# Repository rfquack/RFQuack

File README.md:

[![PlatformIO CI][ci-shield]][ci-url]
[![Contributors][contributors-shield]][contributors-url]
[![Forks][forks-shield]][forks-url]
[![Stargazers][stars-shield]][stars-url]
[![Issues][issues-shield]][issues-url]

<!-- PROJECT LOGO -->
<br />
<div align="center">

  <h3 align="center">RFQuack</h3>

  <p align="center">
    The only RF-analysis tool that quacks!
    <br />
    <br />
    <a href="https://rfquack.org"><strong>Documentation</strong></a>
    |
    <a href="https://arxiv.org/abs/2104.02551"><strong>Research Paper</strong></a>
    <br />
    <br />
    <a href="https://www.youtube.com/playlist?list=PL8hbvIylvVegA6ES-UUfd6sgK-MFNciz5">View Demo</a>
    ·
    <a href="https://github.com/rfquack/RFQuack/issues">Report Bug</a>
    ·
    <a href="https://github.com/rfquack/RFQuack/issues">Request Feature</a>
  </p>
</div>

<!-- ABOUT THE PROJECT -->

## About RFQuack

RFQuack is a versatile RF-analysis tool that allows you to sniff, analyze, and transmit data over the air.

Similarly to RFCat RFQuack has a Python-based scriptable shell that allows you to set parameters, receive, transmit, and so on.

<p align="right">(<a href="#readme-top">back to top</a>)</p>

## Supported Radios

We porting from (and contribute back to) [RadioLib](https://github.com/jgromes/RadioLib). So far, we support:

* __CC1101__ OOK, 2-FSK, 4-FSK, MSK radio module
* __nRF24L01__ 2.4 GHz module
* __RF69__ FSK, OOK radio module

## Supported Arduino Platforms

In principle, RFQuack can run on any board and platform supported by [PlatformIO](https://docs.platformio.org). So far, we tested the following boards:

* [**ESP32**](https://github.com/espressif/rduino-esp32) - ESP32-based boards
* [**Teensy**](https://github.com/PaulStoffregen/cores) - Teensy 2.x, 3.x and 4.x boards

<!-- GETTING STARTED -->
## Getting Started

This is an example of how you may give instructions on setting up RFQuack.

### Prerequisites

You'll need the Protbuf Compiler, a sane Python 3.10, and PlatformIO (which itself requires some dependencies):

- Protobuf Compiler
- Python 3.10.x
- PlatformIO

For more details, please refer to the [Documentation](https://rfquack.org).

<p align="right">(<a href="#readme-top">back to top</a>)</p>

<!-- INSTALLATION -->
## Installation

An easy way to quick start is to have an ESP32 board and a CC1101 and/or RF69 (easier to find) radio module.

```bash
git clone --recursive https://github.com/rfquack/RFQuack
cd RFQuack
pip install -r requirements.pip
vim build.env  # set your parameters and :wq
make clean build flash
```

For more details, please refer to the [Documentation](https://rfquack.org).

<p align="right">(<a href="#readme-top">back to top</a>)</p>

<!-- USAGE -->
## Usage

An easy way to quick start is to connect the dongle via USB and use the CLI.

```shell
$ rfq tty -P /dev/ttyUSB0
2019-04-10 18:04:31 local RFQuack[20877] INFO Transport initialized
2019-04-10 18:04:31 local RFQuack[20877] INFO Transport initialized (QoS = 2): mid = 2

...

RFQuack(/dev/ttyUSB0, 115200,8,N,1)> q.radioA.set_modem_config(modulation="OOK", carrierFreq=434.437)

result = 0
message = 2 changes applied and 0 failed.

RFQuack(/dev/ttyUSB0, 115200,8,N,1)> q.radioA.rx()

result = 0
message =
...
```

For more details, please refer to the [Documentation](https://rfquack.org).

<!-- ROADMAP -->
## Roadmap

- [ ] Add all relevant [RadioLib](https://github.com/jgromes/RadioLib) modules
- [ ] Test with more than 2 radio modules
- [ ] Revisit Python CLI source code and use typed Python 3
- [ ] Integrate with URH and GNU Radio
- [ ] Make a web UI

See the [open issues](https://github.com/rfquack/RFQuack/issues) for a full list of proposed features (and known issues).

<p align="right">(<a href="#readme-top">back to top</a>)</p>

<!-- CONTRIBUTING -->
## Contributing

Contributions are what make the open source community such an amazing place to learn, inspire, and create. Any contributions you make are **greatly appreciated**.

If you have a suggestion that would make this better, please fork the repo and create a pull request. You can also simply open an issue with the proper template.

Don't forget to give the project a star! Thanks again!

1. Fork the project
2. Create your feature branch (`git checkout -b feature/AmazingFeature`)
3. Commit your changes (`git commit -m 'Add some AmazingFeature'`)
4. Run simple integration tests (`make clean build`)
4. Push to the branch (`git push origin feature/AmazingFeature`)
5. Open a Pull Request

<p align="right">(<a href="#readme-top">back to top</a>)</p>

<!-- LICENSE -->
## License

Distributed under the GPL 2 License. See `LICENSE` for more information.

<p align="right">(<a href="#readme-top">back to top</a>)</p>

## Acknowledgments

RFQuack wouldn't exist without the inspiration, feedback, and help received from related tools and awesome humans:

* [RFCat](https://github.com/atlas0fd00m/rfcat)
* [RadioLib](https://github.com/jgromes/RadioLib)
* [RadioHead](https://www.airspayce.com/mikem/arduino/RadioHead/)
* [URH](https://github.com/jopohl/urh)

<p align="right">(<a href="#readme-top">back to top</a>)</p>

<!-- MARKDOWN LINKS & IMAGES -->
<!-- https://www.markdownguide.org/basic-syntax/#reference-style-links -->
[contributors-shield]: https://img.shields.io/github/contributors/rfquack/RFQuack.svg?style=for-the-badge
[contributors-url]: https://github.com/rfquack/RFQuack/graphs/contributors
[forks-shield]: https://img.shields.io/github/forks/rfquack/RFQuack.svg?style=for-the-badge
[forks-url]: https://github.com/rfquack/RFQuack/network/members
[stars-shield]: https://img.shields.io/github/stars/rfquack/RFQuack.svg?style=for-the-badge
[ci-url]: https://github.com/rfquack/RFQuack/actions/workflows/build.yml
[ci-shield]: https://img.shields.io/github/workflow/status/rfquack/RFQuack/PlatformIO%20CI?style=for-the-badge
[stars-url]: https://github.com/rfquack/RFQuack/stargazers
[issues-shield]: https://img.shields.io/github/issues/rfquack/RFQuack.svg?style=for-the-badge
[issues-url]: https://github.com/rfquack/RFQuack/issues
[license-shield]: https://img.shields.io/github/license/rfquack/RFQuack.svg?style=for-the-badge
[license-url]: https://github.com/rfquack/RFQuack/blob/master/LICENSE

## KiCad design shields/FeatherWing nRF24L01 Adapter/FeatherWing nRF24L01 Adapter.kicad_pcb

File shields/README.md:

# Feather Huzzah Shields

We provide two reference shields that work on Feather Huzzah (one for ESP8266 and the other for ESP32), V-Chip's VT-CC112x module and E01-ML01SP2 module (nRF24L01 + PA + PLNA).

## License

Our design is licensed as RFQuack main project, including the symbol and footprint for VT-CC112x.

Referred footprints and symbols, including but not limited to FeatherWing (DIM), are either MIT, Apache, or simply CC0.

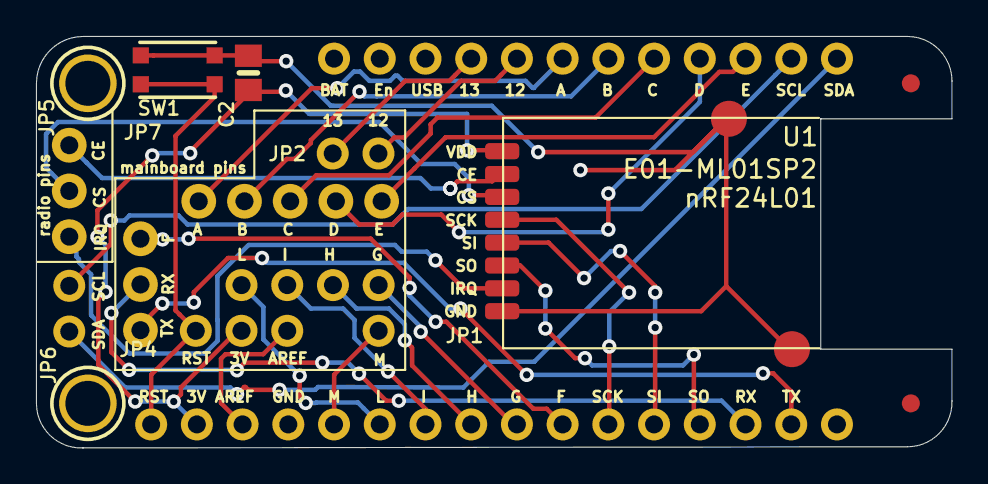
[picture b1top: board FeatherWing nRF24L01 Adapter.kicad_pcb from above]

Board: 2 copper layers, 50.9 x 22.9 mm, 14 parts (0 on the bottom side), 27 nets.

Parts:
C2: 47µF; 0805-NO
FID1, FID2: FIDUCIAL; FIDUCIAL_1MM
JP1: HEADER-1X970MIL; 1X09_ROUND_70
JP2: HEADER-1X570MIL; 1X02_ROUND
JP4, JP5: HEADER-1X376MIL; 1X03_ROUND_76
JP6: HEADER-1X2ROUND; 1X02_ROUND
JP7: HEADER-1X576MIL; 1X05_ROUND_76
MS1: FEATHERWING_NOHOLES
SW1: SWITCH_TACT_SMT4.6X2.8; BTN_KMR2_4.6X2.8
U1: nRF24L01_PA_LNA_E01_ML01SP2; E01-ML01SP2
U$7, U$8: MOUNTINGHOLE2.5; MOUNTINGHOLE_2.5_PLATED

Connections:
3.3V: C2.2, JP1.8, MS1.2, U1.1
/A: JP7.1, MS1.23
/AREF: JP1.7, MS1.3
/B: JP7.2, MS1.22
/C: JP7.3, MS1.21
/CE: JP5.3, U1.2
/CS: JP5.2, U1.3
/D: JP7.4, MS1.20
/E: JP7.5, MS1.19
/F: JP4.1, MS1.10
/G: JP1.1, MS1.9
/H: JP1.2, MS1.8
/I: JP1.3, MS1.7
/IRQ: JP5.1, U1.7
/L: JP1.4, MS1.6
/M: JP1.5, MS1.5
/MISO: MS1.13, U1.6
/MOSI: MS1.12, U1.5
/RST: JP1.9, MS1.1, SW1.B, SW1.B'
/RX: JP4.2, MS1.14
/SCK: MS1.11, U1.4
/TX: JP4.3, MS1.15
GND: C2.1, SW1.A, SW1.A', U1.8, U1.9, U1.10
unnamed: JP2.1, MS1.25
unnamed: JP2.2, MS1.24
unnamed: JP6.1, MS1.18
unnamed: JP6.2, MS1.17

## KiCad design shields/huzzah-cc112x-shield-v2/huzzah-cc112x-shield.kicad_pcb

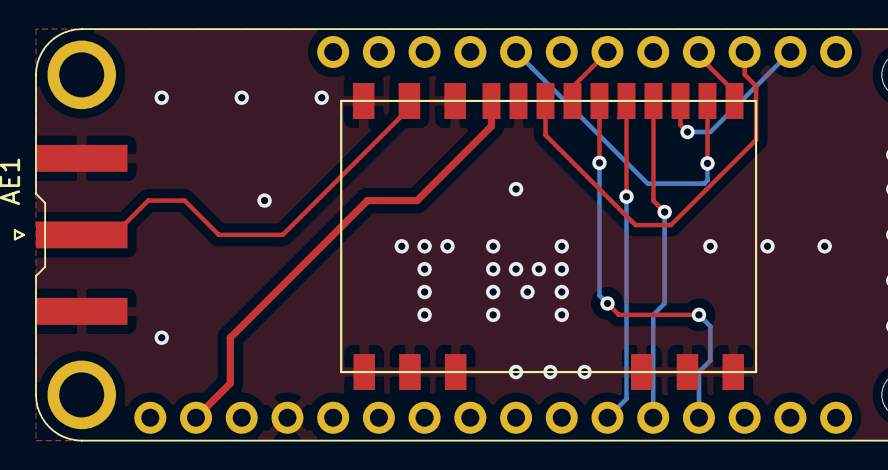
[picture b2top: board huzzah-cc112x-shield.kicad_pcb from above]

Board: 2 copper layers, 3 parts (0 on the bottom side), 11 nets.

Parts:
AE1: Antenna; SMA_Amphenol_132289_EdgeMount
MS1: FEATHERWING; FEATHERWING_DIM
U1: VT-CC112x-433M

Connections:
/3V3: MS1.2, U1.10
/CS: MS1.19, U1.8
/GND: AE1.2, MS1.4, U1.9, U1.11, U1.13, U1.14, U1.15, U1.16, U1.17, U1.18, U1.19
/GPIO3: MS1.24, U1.2
/ISR: MS1.18, U1.3
/ISR_PKT: MS1.22, U1.7
/RST: MS1.20, U1.1
/SCLK: MS1.11, U1.5
/SI: MS1.12, U1.4
/SO: MS1.13, U1.6
unnamed: AE1.1, U1.12

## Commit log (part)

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2019-05-07 Merge
2019-05-07 Fixing README
2019-05-07 Fixed Python syntax in the README.md
2019-10-26 Added missing configuration example for RFQuack-huzzah-rf69hw Added example credentials file Updated .gitignore to track example configuration for scret files (*credentials*.example)
2019-11-04 Added API support for fixed/variable packet format
2019-11-04 added example for RFQuack-huzzah32-rf69hw
2019-11-04 fixed examples to avoid conflicts with RadioHead
2019-11-04 fixed banner
2019-11-04 support for variable/fixed packet format
2019-11-04 regenerated protobuf python types
2019-11-04 default TX repeat value
2019-11-04 fixed buggy log printer
2019-11-04 macro comment for dev output
2019-11-05 CLI now lives in separate repo at rfquack/RFQuack-cli
2019-11-05 image align in README
2019-11-15 added FeatherWing nRF24L01 adapter
2019-11-15 changed nRF24 module to E01-ML01SP2
2019-12-08 Switch to RadioLib + Multiple Radio Support
2019-12-09 Removed references to RadioHAL
2019-12-10 Minor fixes.
2019-12-16 Added .pio* ignore pattern
2019-12-16 Removed old examples from RadioLib branch
2019-12-16 Snapshot
2019-12-17 [CC1101] Stop FIFO polling after 10mS
2019-12-17 User Serial1 for logging
2019-12-17 Added pio* ignore pattern
2019-12-17 Added makefile job to make examples
2020-01-22 [WIP] Modularization
2020-01-23 Modularization
2020-02-18 Fixed wrong return type
2020-02-19 [Modules] Better reply
2020-02-20 [Radio] Added setPromiscuousMode, getRSSI, isCarrierDetected
2020-02-20 Examples updated
2020-02-20 Examples setup updated
2020-02-20 Minor fixes + warnings fixes
2020-02-20 Moved module's hooks to a separated folder + documentation
2020-02-20 Yet another refactor to rfquack_radio.h
2020-02-25 Added mouse jack module.
2020-02-27 Fix rfquack_transport_setup()
2020-02-27 Removed useless loop
2020-02-28 Added parameter 'wait_time' in FrequencyScannerModule
2020-02-28 Small fixes
2020-03-02 [nRF24] Driver fix.
2020-03-03 Added HUZZAH32 as build target
2020-03-03 Typo
2020-03-04 Missing directory
2020-03-16 HelloWorldModule sample module
2020-04-09 Set a longer keep-alive value
2020-04-10 Added getChipName(), used for presets in FrequencyScannerModule
2020-04-10 [CC1101] Better gain settings + added method for manual calibration.
2020-04-10 Moved RadioLib dependency to https://github.com/rfquack/RadioLib
2020-04-10 [GuessingModule] Documentation and stop() method
2020-04-10 [nRF24] Missing writeRegister() implementation.
2020-04-10 Removed HelloWorldModule.h from pre-loaded modules
2020-04-11 [Docker] Automatically fill RFQUACK_TOPIC_PREFIX with an UUID
2020-04-11 [Examples] Stressing the fact that RFQUACK_TOPIC_PREFIX should be unique.
2020-04-11 [Keywords] Removed unsupported radios.
2020-04-11 [Transport] Added broadcast topic "any" to address any dongle: Example: any/in/get/...
2020-05-01 Small fixes + time statistics.
2020-05-13 Added supporto for MQTT over SSL
2020-05-14 Small fix
2020-05-15 Added .vscode/*
2020-05-15 Added lib/nanopb to ignore patterns
2020-05-15 Removed images + promoted section
2020-05-15 Nanopb latest version
2020-05-15 Pipfile to manage Python deps
2020-11-24 Client ID matches Unique ID
2020-11-27 Firmware compatible with NetQuack
2021-04-06 Adding RFM69
2021-04-06 Added projects section
2021-04-12 Added new shield
2021-04-12 Updated deps and EP
2021-04-12 Updated README.md with build-only example
2021-04-13 Smarter helper Makefile now supports flashing
2021-04-13 New repo URL in library.properties
2021-04-13 Fixed my-entrypoint.sh to build only or upload
2021-04-14 Using God mode
2021-04-16 Missing `_mod->`
2021-04-21 Removed truncated comment
2021-04-21 Added new modulation schemes
2021-04-24 Switched to submodule for RadioLib
2021-06-02 Bump urllib3 from 1.26.4 to 1.26.5
    Bumps [urllib3](https://github.com/urllib3/urllib3) from 1.26.4 to 1.26.5.
    - [Release notes](https://github.com/urllib3/urllib3/releases)
    - [Changelog](https://github.com/urllib3/urllib3/blob/main/CHANGES.rst)
    - [Commits](https://github.com/urllib3/urllib3/compare/1.26.4...1.26.5)
    ---
    updated-dependencies:
2021-09-16 Updated RadioLib to master HEAD
2021-09-16 Upgraded Python deps
2021-09-16 Removed Protobuf Python-compiled header
2021-09-19 Add default src/main.cpp to ignore patterns
2021-09-19 Cleaned white spaces and newlines
2021-09-19 Added mock platformio.ini file
2021-09-19 Added pre/post scripts
2021-09-19 Reformatted and updated library.json
2021-09-19 Added pio run
2021-09-19 Added s/pio/platformio/
2021-09-20 Added pipenv run
2021-09-20 Added pio lib install
2021-09-24 Workflow working on act
2021-09-27 Removed macos-latest and windows-latest
2022-01-26 Added proto target to Makefile
    Reinstated proto target in Makefile to resolve build issues.
2022-06-03 Bump bottle from 0.12.19 to 0.12.20
    Bumps [bottle](https://github.com/bottlepy/bottle) from 0.12.19 to 0.12.20.
    - [Release notes](https://github.com/bottlepy/bottle/releases)
    - [Changelog](https://github.com/bottlepy/bottle/blob/master/docs/changelog.rst)
    - [Commits](https://github.com/bottlepy/bottle/compare/0.12.19...0.12.20)
    ---
    updated-dependencies:
2022-08-24 updated outdated packages
2022-08-24 added new exmaple
2022-08-30 clean up
2022-08-30 rollback board
2022-08-30 README linting
2022-08-30 Added favicon square format
2022-09-02 - Code of conduct - Contributing guidelines - Security policy - Issue templates
2022-09-02 Update contribution guidelines
2022-09-03 radiolib 5.3.0 changes (#23)
2022-09-03 Updated RadioLib
2022-09-23 Bump protobuf from 3.18.0 to 3.18.3
    Bumps [protobuf](https://github.com/protocolbuffers/protobuf) from 3.18.0 to 3.18.3.
    - [Release notes](https://github.com/protocolbuffers/protobuf/releases)
    - [Changelog](https://github.com/protocolbuffers/protobuf/blob/main/generate_changelog.py)
    - [Commits](https://github.com/protocolbuffers/protobuf/compare/v3.18.0...v3.18.3)
    ---
    updated-dependencies:
2022-11-07 adding missing code to CC1101 and implementing full promiscious mode with custom or missing syncwords (needs GPIO02 connection to work)
2022-11-15 Moved getters/setters into RadioLib
2022-11-15 Better code documentation
2022-11-15 Ignoring docs/reference
2022-11-15 Compact Dockerfile
2022-11-15 Compact library.json
2022-11-15 The Makefile is the new entry point
2022-11-15 No entry point for docker
2022-11-15 Removing pre/post PlatformIO build scripts
2022-11-15 Simpler examples
2022-11-15 Removed client/
2022-11-15 build.env with 3 RFs
2022-11-16 make clean now removes Protobuf-generated code
2022-11-16 mypy protobuf-types
2022-11-16 Build system advancements
2022-11-16 GA: removed apt deps
2022-11-16 GA: bump python version
2022-11-16 GA: RadioLib is now a dep
2022-11-16 GA: checkout submodules
2022-11-16 First proper release of the docs
2022-11-16 GA: MkDocs + py310
2022-11-16 Improving README
2022-11-18 Fixes minor typo on support faq page
2022-11-18 Fixes minor typo on support faq page (#29)
2022-11-20 New rfquack/RadioLib version
2022-11-21 _syncWordLength is now in RFQCC1101 wrapper
2022-11-21 [RadioLib] PR#613 reviews
2022-11-26 Adding RadioLib as a dependency
2022-11-26 New requirements.pip
2022-11-26 Docs update
2022-11-26 Updated lib/RadioLib
2022-11-26 - No more SoftwareSerial logging - logging goes all to `Serial` if enabled
2022-11-26 Using logging macros
2022-11-27 Update RadioLib
2022-11-27 Send message at boot to help CLI find the dongle
2022-11-27 Cherry picked some changes from @akito45's fork
2022-11-28 Update Dockerfile to make use of python 3.10 slim base image
2022-11-28 Update Dockerfile to make use of python 3.10 slim base image (#31)
2022-11-28 Fix #30
2022-11-28 Fix license
2022-11-28 Adding library of examples
2022-11-29 [RadioLib] update to latest master
2022-11-30 [DEMOs] Adding demo material
2022-12-01 - Better console - Minor tweaking
2022-12-02 Addresses #32
2022-12-03 Datasheets and pinouts
2022-12-03 Better client introspection and auto-completion
2022-12-03 [BHEU2022] Demo are final
2022-12-03 RadioLib and nRF24 fixes
2022-12-05 Better template main.cpp
2022-12-05 Force ENV format for build.env
2022-12-05 Added non-working example for 2xCC1101 + nRF24
2022-12-09 Bump certifi from 2022.9.24 to 2022.12.7
    Bumps [certifi](https://github.com/certifi/python-certifi) from 2022.9.24 to 2022.12.7.
    - [Release notes](https://github.com/certifi/python-certifi/releases)
    - [Commits](https://github.com/certifi/python-certifi/compare/2022.09.24...2022.12.07)
    ---
    updated-dependencies:
    - dependency-name: certifi
2022-12-11 CI/CD `build.env`
2022-12-11 BH Arsenal 2022 Europe PPT
2023-01-24 Update README.md
    Thanks @bazuchan for the heads up.
2023-02-20 Bump ipython from 8.6.0 to 8.10.0 (#37)
    Bumps [ipython](https://github.com/ipython/ipython) from 8.6.0 to 8.10.0.
    - [Release notes](https://github.com/ipython/ipython/releases)
    - [Commits](https://github.com/ipython/ipython/compare/8.6.0...8.10.0)
    ---
    updated-dependencies:
    - dependency-name: ipython
2023-02-20 Bump gitpython from 3.1.29 to 3.1.30
    Bumps [gitpython](https://github.com/gitpython-developers/GitPython) from 3.1.29 to 3.1.30.
    - [Release notes](https://github.com/gitpython-developers/GitPython/releases)
    - [Changelog](https://github.com/gitpython-developers/GitPython/blob/main/CHANGES)
    - [Commits](https://github.com/gitpython-developers/GitPython/compare/3.1.29...3.1.30)
    ---
    updated-dependencies:
2023-06-19 build.env for EvilCrowRF-V2
2023-06-19 build.env for EvilCrowRF-V2 (#47)
2023-06-19 Deployed cabbe3f with MkDocs version: 1.4.3
2024-11-02 Bump gitpython from 3.1.29 to 3.1.30 (#38)
    Bumps [gitpython](https://github.com/gitpython-developers/GitPython) from 3.1.29 to 3.1.30.
    - [Release notes](https://github.com/gitpython-developers/GitPython/releases)
    - [Changelog](https://github.com/gitpython-developers/GitPython/blob/main/CHANGES)
    - [Commits](https://github.com/gitpython-developers/GitPython/compare/3.1.29...3.1.30)
    ---
    updated-dependencies:
2024-11-02 Deployed 3a868df with MkDocs version: 1.6.1
2024-11-02 Bump idna from 3.4 to 3.7
    Bumps [idna](https://github.com/kjd/idna) from 3.4 to 3.7.
    - [Release notes](https://github.com/kjd/idna/releases)
    - [Changelog](https://github.com/kjd/idna/blob/master/HISTORY.rst)
    - [Commits](https://github.com/kjd/idna/compare/v3.4...v3.7)
    ---
    updated-dependencies:
2024-11-02 Bump urllib3 from 1.26.12 to 1.26.19
    Bumps [urllib3](https://github.com/urllib3/urllib3) from 1.26.12 to 1.26.19.
    - [Release notes](https://github.com/urllib3/urllib3/releases)
    - [Changelog](https://github.com/urllib3/urllib3/blob/main/CHANGES.rst)
    - [Commits](https://github.com/urllib3/urllib3/compare/1.26.12...1.26.19)
    ---
    updated-dependencies:
2024-11-02 Bump gitpython from 3.1.30 to 3.1.41
    Bumps [gitpython](https://github.com/gitpython-developers/GitPython) from 3.1.30 to 3.1.41.
    - [Release notes](https://github.com/gitpython-developers/GitPython/releases)
    - [Changelog](https://github.com/gitpython-developers/GitPython/blob/main/CHANGES)
    - [Commits](https://github.com/gitpython-developers/GitPython/compare/3.1.30...3.1.41)
    ---
    updated-dependencies:
2024-11-02 Bump black from 22.10.0 to 24.3.0
    Bumps [black](https://github.com/psf/black) from 22.10.0 to 24.3.0.
    - [Release notes](https://github.com/psf/black/releases)
    - [Changelog](https://github.com/psf/black/blob/main/CHANGES.md)
    - [Commits](https://github.com/psf/black/compare/22.10.0...24.3.0)
    ---
    updated-dependencies:

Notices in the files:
shields/huzzah-cc112x-shield-v2/huzzah-cc112x-shield.kicad_pcb:
License GPLv2
